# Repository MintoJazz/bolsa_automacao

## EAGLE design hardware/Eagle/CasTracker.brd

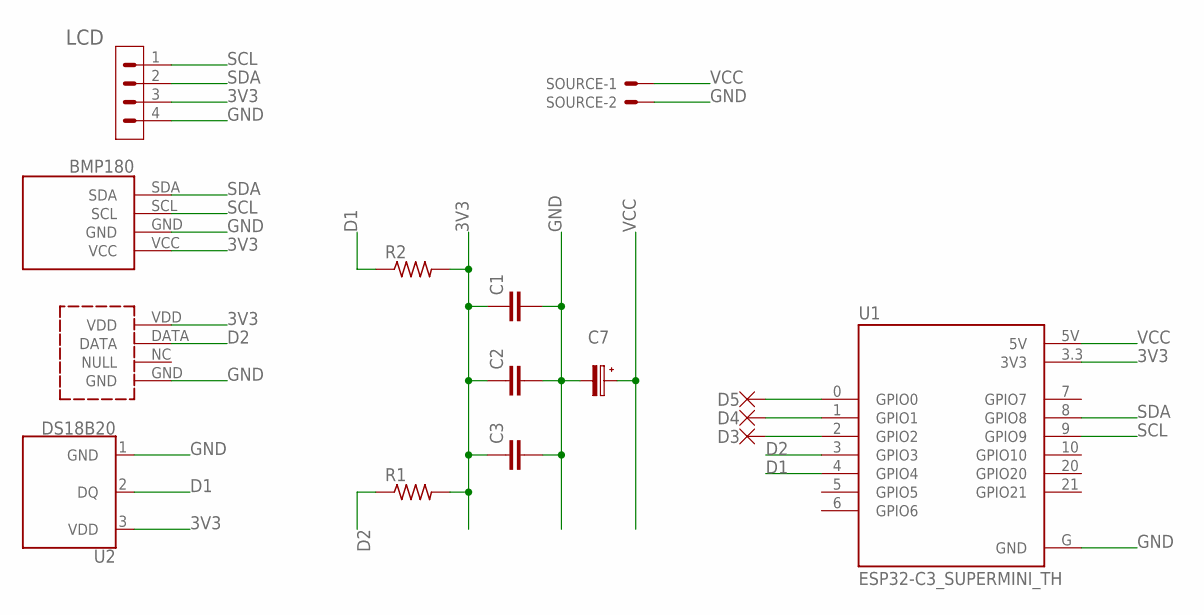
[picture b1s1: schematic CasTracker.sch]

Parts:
BMP180: GY-68-BMP180
C1, C2, C3: C2.5/2; C2.5-2
C7: 100u; CAPPRD508W65D1000H1100B
D3, D4, D5: PAD; 2.54/1.0
DHT22: DHT22
LCD: PINHD-1X4/90; 1X04/90
R1, R2: R-US_0204/2V; 0204V
SOURCE: CON-MOLEX_22-23-2021
U1: ESP32-C3_SUPERMINI_TH; MODULE_ESP32-C3_SUPERMINI_TH
U2: DS18B20; TO-92-AMMO

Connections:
3V3: BMP180.VCC, C1.1, C2.1, C3.1, DHT22.VDD, LCD.3, R1.2, R2.2, U1.3.3 (3V3), U2.3 (VDD)
D1: R2.1, U1.4 (GPIO4), U2.2 (DQ)
D2: DHT22.DATA, R1.1, U1.3 (GPIO3)
GND: BMP180.GND, C1.2, C2.2, C3.2, C7.2 (-), DHT22.GND, LCD.4, SOURCE.2, U1.G (GND), U2.1 (GND)
PAD1: D5.1, U1.0 (GPIO0)
PAD2: D4.1, U1.1 (GPIO1)
PAD3: D3.1, U1.2 (GPIO2)
SCL: BMP180.SCL, LCD.1, U1.9 (GPIO9)
SDA: BMP180.SDA, LCD.2, U1.8 (GPIO8)
VCC: C7.1 (+), SOURCE.1, U1.5V

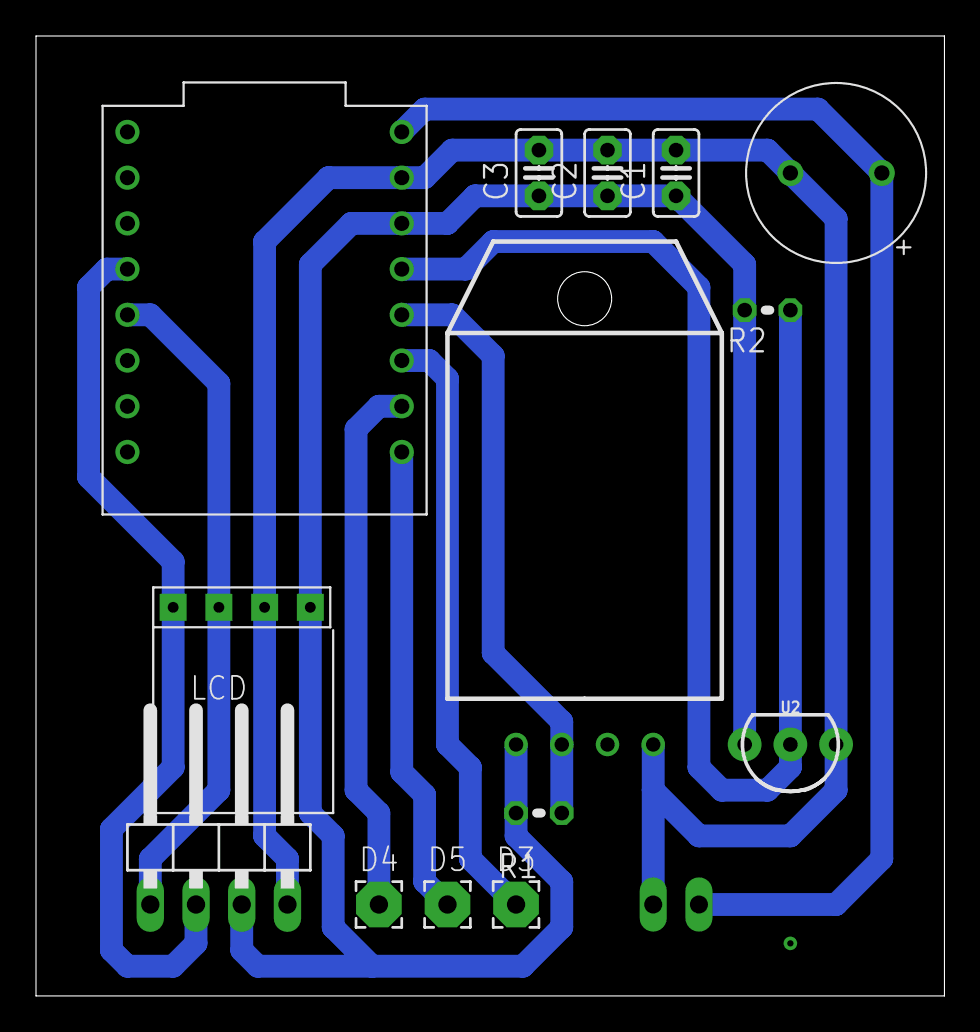
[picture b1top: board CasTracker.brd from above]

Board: 2 copper layers, 50.5 x 53.3 mm, 15 parts (1 on the bottom side), 10 nets.

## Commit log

2025-09-14 CommitInicial
2025-09-14 publisher_v2
2025-09-14 publisherv2.0.1
2025-10-05 Semana6
2025-10-12 update10out2025
2025-12-15 update15dec2025
2025-12-15 refatoração da estrutura
2025-12-17 update17dec2025

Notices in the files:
parts and their libraries:
SparkFun-Sensors: Licensing: Creative Commons ShareAlike 4.0 International - https://creativecommons.org/licenses/by-sa/4.0
